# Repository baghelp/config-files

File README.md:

# config-files

copy all of these files into your ~/ directory, run `bash setup-env.sh`, and things _should_ "just work"

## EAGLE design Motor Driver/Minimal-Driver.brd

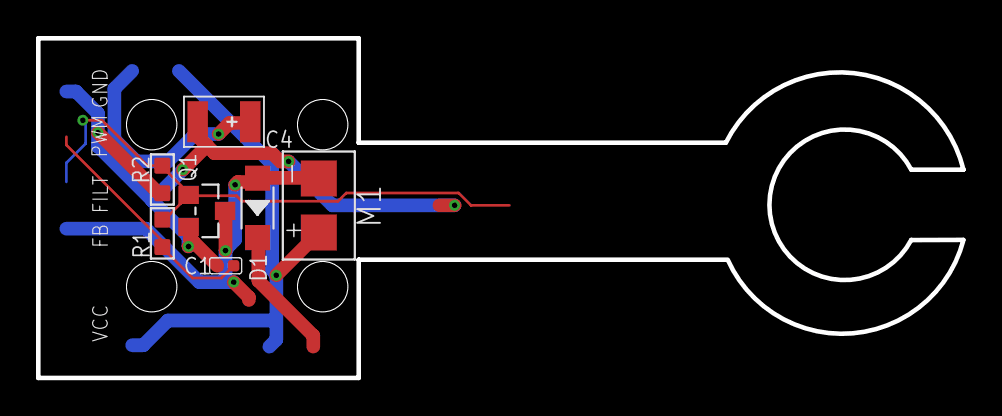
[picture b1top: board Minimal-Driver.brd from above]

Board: 2 copper layers, 51.4 x 18.9 mm, 7 parts (0 on the bottom side), 5 nets.

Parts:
C1: 1uf; C0402
C4: 100uf; AVX-B
D1: 20V-500MA; SOD-123
M1: MOTOR_PADS
Q1: CJ2302; SOT-23
R1: 100R; R0603
R2: 10K 1/10W; R0603

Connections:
FILTERED: Q1.1, R1.2, R2.2
FLYBACK: D1.+, M1.V-, Q1.3
GND: C1.1, C4.-, Q1.2, R2.1
PWM: C1.2, R1.1
VCC: C4.+, D1.-, M1.V+

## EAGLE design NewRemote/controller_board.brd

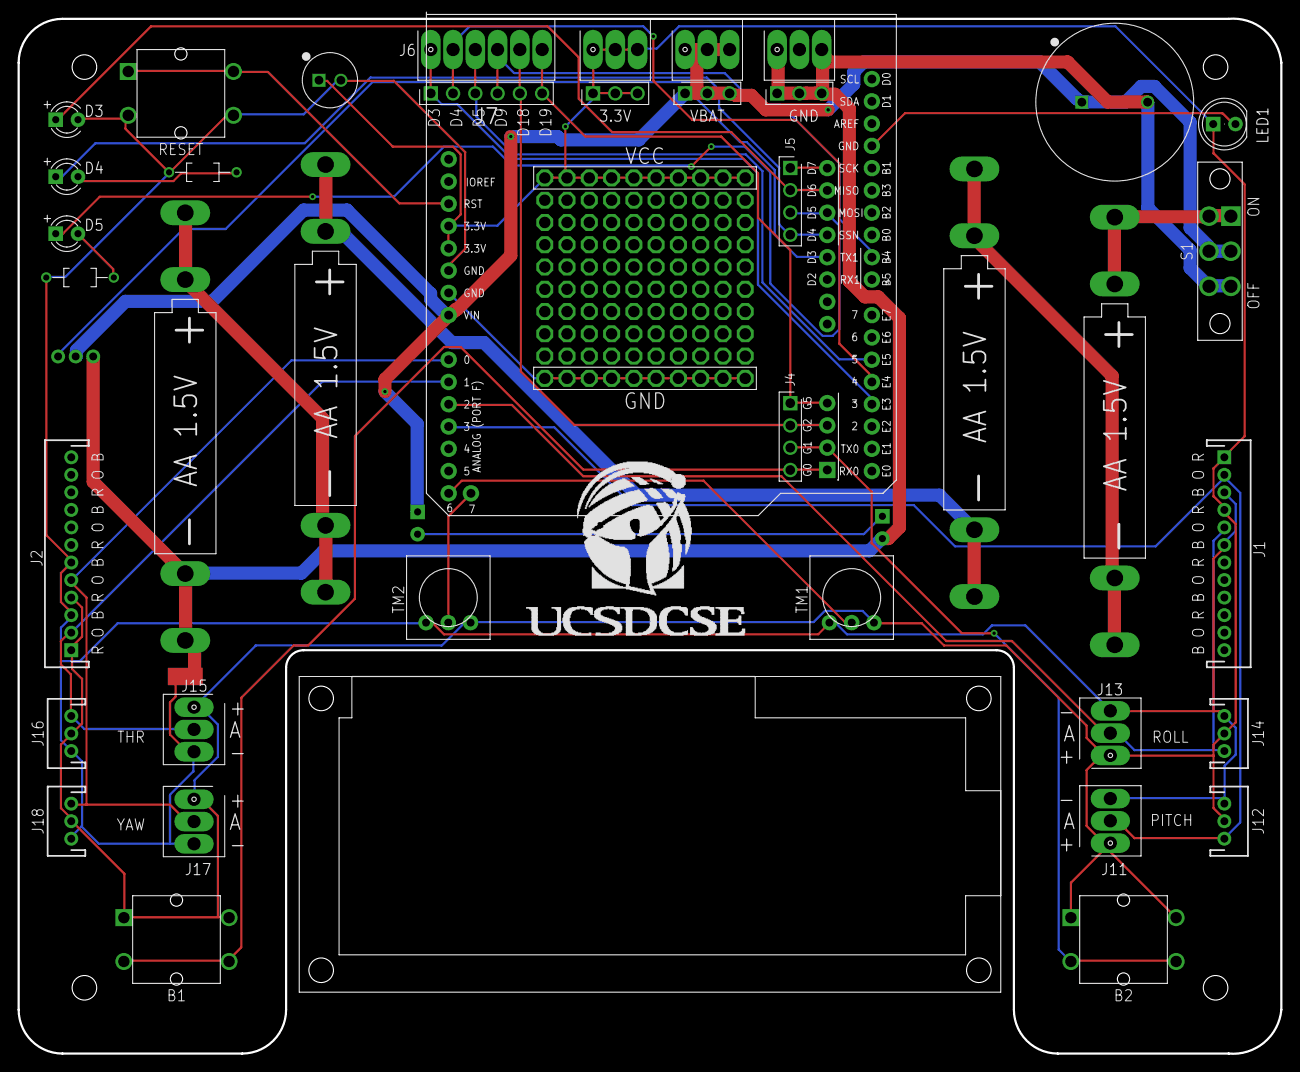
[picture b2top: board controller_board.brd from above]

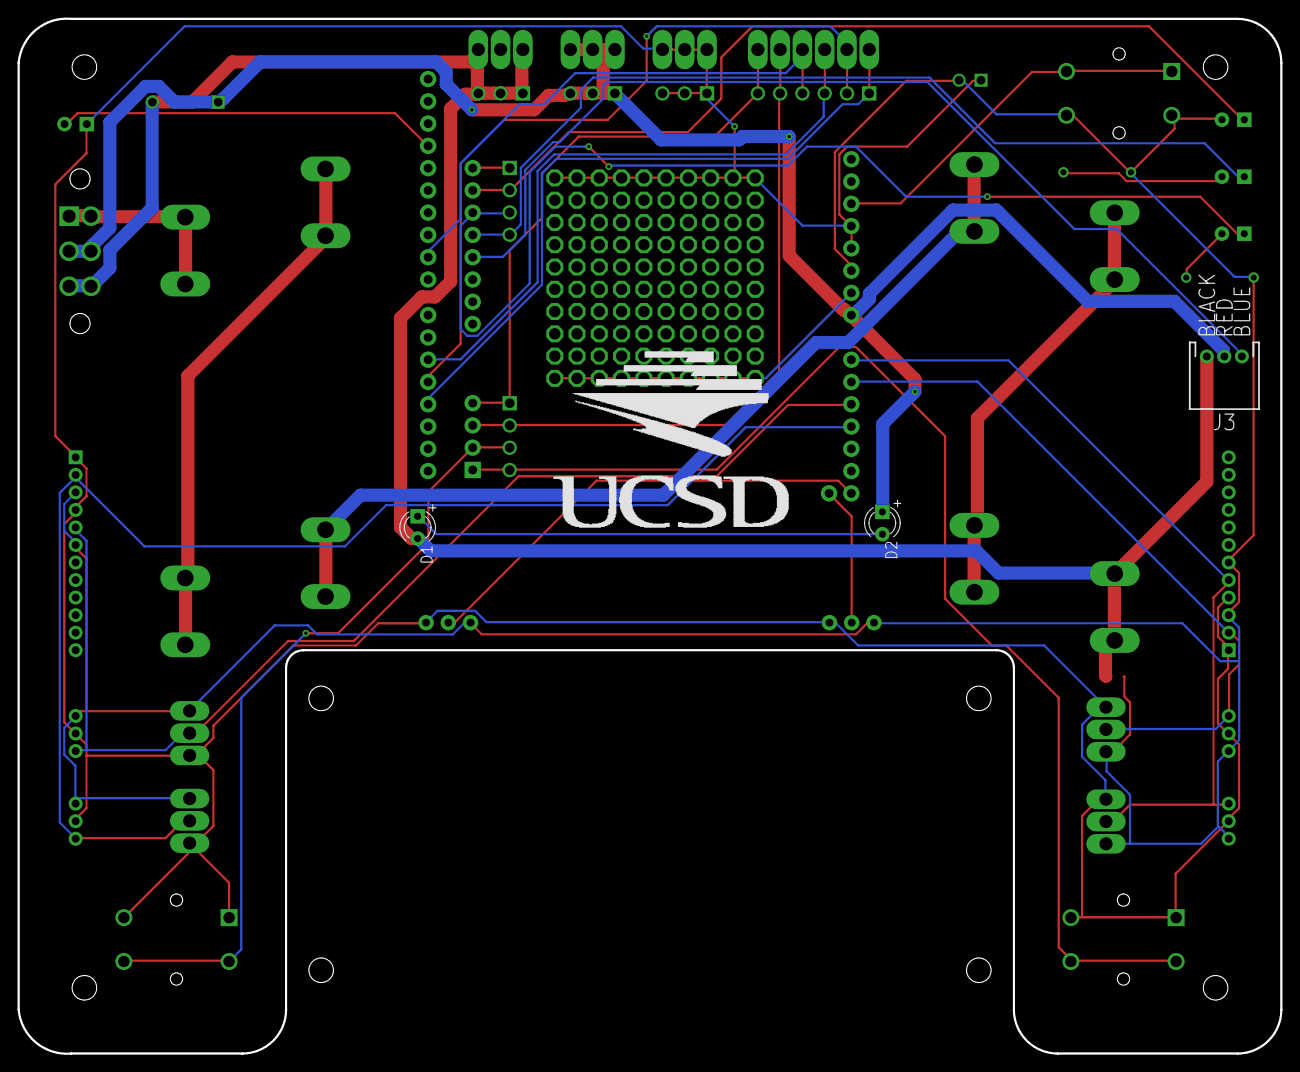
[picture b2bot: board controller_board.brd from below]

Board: 2 copper layers, 144.0 x 118.0 mm, 48 parts (4 on the bottom side), 31 nets.

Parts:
3.3V: SCREW-TERMINAL-1X3-2.54MM
B1, B2: BUTTON-TACTILE-SQUARE; BUTTON-TACTILE-SQUARE-ADAFRUIT1010
BATT1, BATT2, BATT3, BATT4: BATTERY-AA-CLIP; BATTERY-AA-BK-92
C1: CAPPRD750W80D1800H2200P
C2: CAPPRD250W80D630H1220P
D1, D2: LED3MM
D3: BLUE; LED3MM
D4: RED; LED3MM
D5: GREEN; LED3MM
F1: SHORT
GND: SCREW-TERMINAL-1X3-2.54MM
J1, J2: FRSKY-GIMBAL; JST-13-PTH
J3: WIRE-HARNESS-SPARKFUN-9915
J4, J5: HDRV4W63P254_4X1_1016X254H838_HS
J6: HEADER-0.1IN-6POS-SCREW; SCREW-TERMINAL-1X6-2.54MM
J7: HEADER-0.1IN-6POS-FEMALE; HDRV6W63P254_6X1_1524X254H838_HS
J8, J9, J10: HDRV3W63P254_3X1_762X254H838_HS
J11, J13, J15, J17: SCREW-TERMINAL-1X3-2.54MM
J12, J14, J16, J18: JST_3PIN_GND_VDD_SIG; JST-3-PTH-REVERSE
LCD: SPARKFUN_LCD_33
LED1: LED5MM
OUTLINE: CONTROLLER_OUTLINE
R4, R5: RESAD770W45L370D210_HS
RESET: BUTTON-TACTILE-SQUARE; BUTTON-TACTILE-SQUARE-ADAFRUIT1010
S1: POWER-SWITCH-MFS201N-9-Z
TM1, TM2: TRIM-3386
U$1: CSE_LOGO_30X20MM
U$2: UCSD_LOGO_COMBINED_26X20MM
U$3: PROTO-AREA-10X10
U$4: ATMEGA128RFA1-BOB; ATMEGA128RFA1
VBAT: SCREW-TERMINAL-1X3-2.54MM

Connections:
+3V3: 3.3V.1, 3.3V.2, 3.3V.3, B1.P, B1.P2, B2.P, B2.P2, C2.1, J1.1, J1.4, J2.1, J2.4, J8.1, J8.2, J8.3, J11.1, J12.2, J13.1, J14.2, J15.1, J16.2, J17.1, J18.2, LED1.A, TM1.3, TM2.3, U$3.P$11, U$3.P$12, U$3.P$13, U$3.P$14, U$3.P$15, U$3.P$16, U$3.P$17, U$3.P$18, U$3.P$19, U$3.P$20, U$4.3.3V, U$4.3.3V1
BATGND: BATT4.N1, BATT4.N2, C1.2, D1.K, F1.B, GND.1, GND.3, J3.BLACK, J10.1, J10.2, J10.3, S1.P$3, S1.P$6
BTN1: B1.S, B1.S2, J4.4, U$4.PG0
BTN2: B2.S, B2.S2, J4.3, U$4.PG1
D3: J6.1, J7.1, U$4.J2.D3
D4: J6.2, J7.2, U$4.PE4
D5: J6.3, J7.3, U$4.J2.D5
D9: J6.4, J7.4, U$4.J2.D9
D18: J4.2, J6.5, J7.5, U$4.PG2
D19: J4.1, J6.6, J7.6, U$4.PG5
GND: C2.2, D3.K, F1.A, J1.3, J1.6, J2.3, J2.6, J11.3, J12.1, J13.3, J14.1, J15.3, J16.1, J17.3, J18.1, LED1.K, R4.1, R5.1, RESET.S, RESET.S2, TM1.1, TM2.1, U$3.P$1, U$3.P$2, U$3.P$3, U$3.P$4, U$3.P$5, U$3.P$6, U$3.P$7, U$3.P$8, U$3.P$9, U$3.P$10, U$4.GND, U$4.GND1, U$4.GND2
LED_BLUE: D3.A, J5.2, U$4.PD6
LED_GREEN: D5.A, J5.3, U$4.PD5
LED_RED: D4.A, J5.4, U$4.PD4
unnamed: BATT1.N1, BATT1.N2, BATT2.P1, BATT2.P2
unnamed: BATT2.N1, BATT2.N2, BATT3.P1, BATT3.P2
unnamed: BATT3.N1, BATT3.N2, BATT4.P1, BATT4.P2
unnamed: D4.K, R4.2
unnamed: BATT1.P1, BATT1.P2, S1.P$1, S1.P$4
unnamed: D5.K, R5.2
unnamed: J5.1, U$4.PD7
unnamed: D1.A, D2.K
PITCH: J1.2, J11.2, J12.3, U$4.A3
POT1: TM1.2, U$4.A6
POT2: TM2.2, U$4.A7
RESET: RESET.P, RESET.P2, U$4.RESET
ROLL: J1.5, J13.2, J14.3, U$4.A2
THROTTLE: J2.2, J15.2, J16.3, U$4.A1
TX1: J3.BLUE, U$4.TX1
VBAT: C1.1, D2.A, J3.RED, J9.1, J9.2, J9.3, S1.P$2, S1.P$5, U$4.VCC, VBAT.1, VBAT.2, VBAT.3
YAW: J2.5, J17.2, J18.3, U$4.A0

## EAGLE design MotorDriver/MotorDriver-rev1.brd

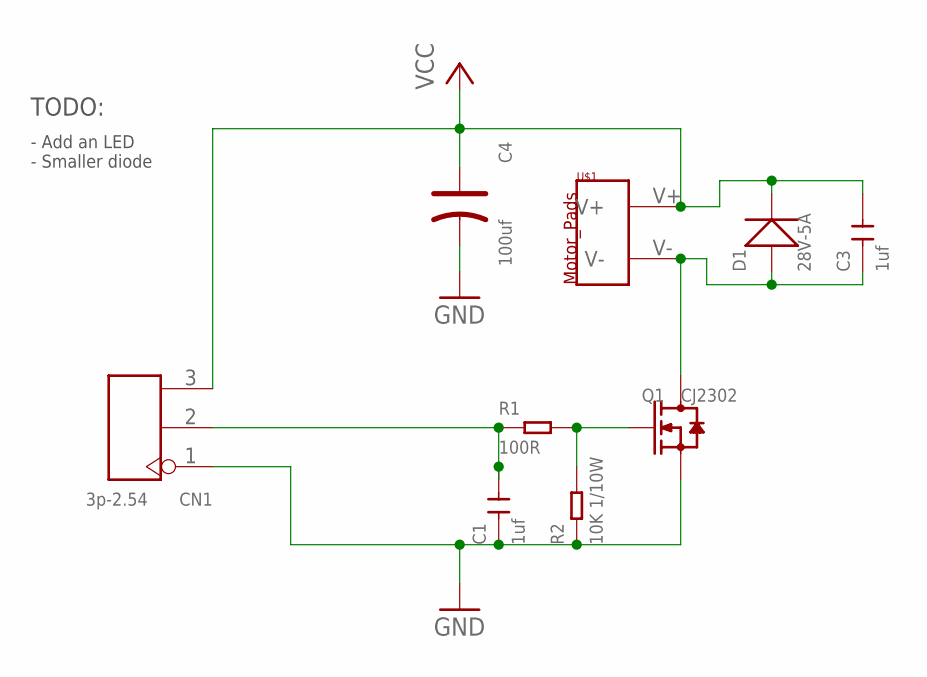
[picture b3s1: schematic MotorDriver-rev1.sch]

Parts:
C1: 1uf; C0402
C3: 1uf; C0603
C4: 100uf; AVX-B
CN1: 3p-2.54; H3-2.54
D1: 28V-5A; DO-214AA
Q1: CJ2302; SOT-23
R1: 100R; R0603
R2: 10K 1/10W; R0603
U$1: MOTOR_PADS

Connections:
GND: C1.1, C4.-, CN1.1, Q1.2 (S), R2.1
unnamed: C1.2, CN1.2, R1.1
unnamed: Q1.1 (G), R1.2, R2.2
unnamed: C3.1, D1.+, Q1.3 (D), U$1.V-
VCC: C3.2, C4.+, CN1.3, D1.-, U$1.V+

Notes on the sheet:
TODO:
- Add an LED - Smaller diode

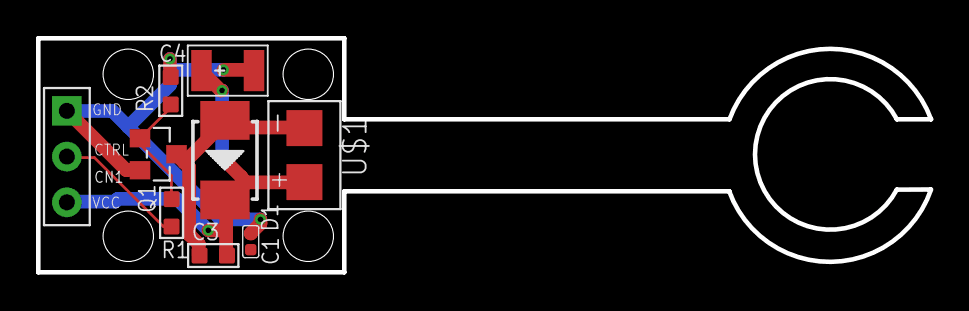
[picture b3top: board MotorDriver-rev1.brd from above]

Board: 2 copper layers, 49.6 x 13.0 mm, 9 parts (0 on the bottom side), 5 nets.

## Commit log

2016-04-09 remove code that was a solution for part of lab 3
2016-04-18 Rev1 with todos
2016-12-03 removed purposeless file
2016-12-03 added vim config
2016-12-05 changes to .vimrc
2017-03-17 New remote, new motor driver
2017-03-17 Test Stand
2017-03-19 A bunch of new parts
2017-03-19 Fix mounting holes on platform. Adjust braces so they serve as landing areas for motors. thickness for 1/8 in plywood.
2017-03-19 missing part numbers
2017-03-19 Move some stuff to other repos and cleanup
2017-03-19 cleanup
2017-03-26 reorg to make it a arduino sketchbook-a
2017-04-21 initialize_with_starter_code
2017-06-03 newer vimrc
2017-06-03 better vimrc
2017-07-06 remove files accientally added
2017-07-06 remove more accidental files
2017-07-06 more accidental files
2017-07-06 accidental file
2022-01-18 no more line-wrap, change tab width to 4 spaces
2025-05-25 fix: I don't like ron colorscheme anymore, updating to default. Also commenting out code that doesn't work anyways
2025-05-27 feat: getting rid of old configs that I no longer use. Pulling in all my vim stuff instead
2025-05-27 feat: adding some instructions
2026-01-28 feat: cleaned up to allow easier installation on rpi's for development
2026-01-29 Update README.md
    clearer instructions
